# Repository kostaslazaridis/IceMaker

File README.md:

I came across a broken ice maker. Eager to repair it, I discovered that the original PCB was destroyed due to a burned-out IC, making it irreparable. Instead of giving up, I decided to reverse engineer the ice maker's electronics to recreate a working control board from scratch.
https://www.youtube.com/watch?v=2SMoJ112lBk&t=18s

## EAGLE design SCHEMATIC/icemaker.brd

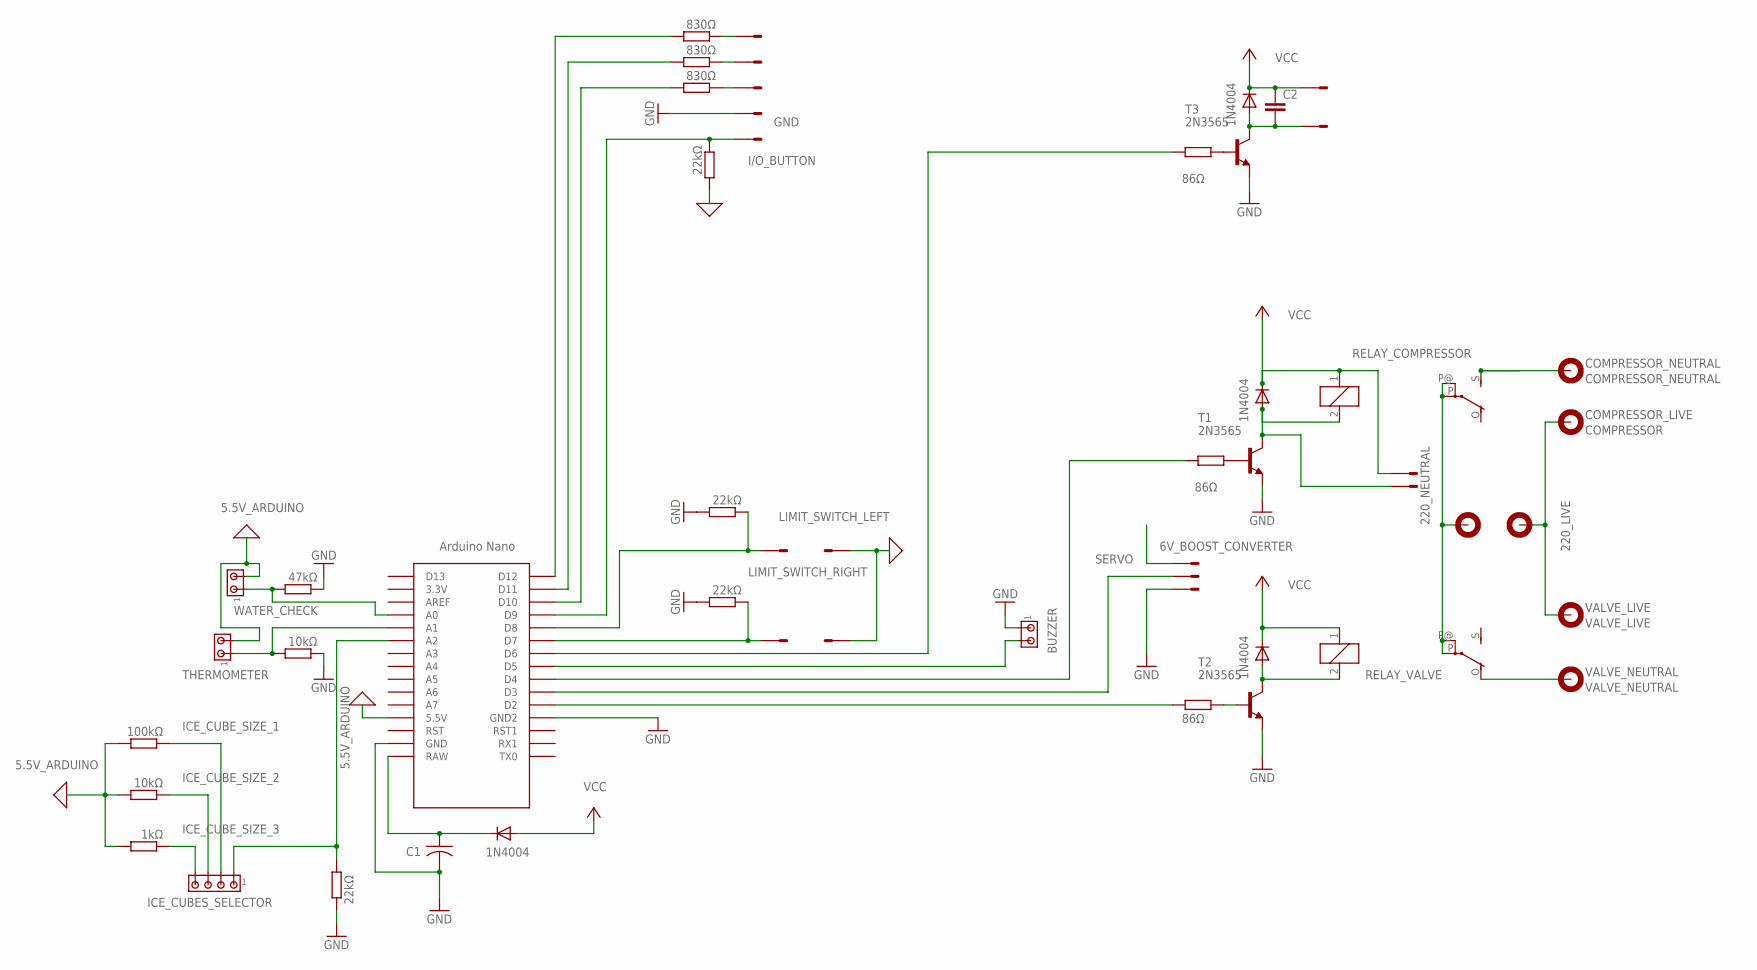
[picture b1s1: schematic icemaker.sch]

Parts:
220_LIVE: 220_LIVE; 2,8-PAD
220_NEUTRLA: 220_NEUTRAL; 2,8-PAD
BUZZER: MTA02-156; 1X2MTA
C1: C-US050-025X075; C050-025X075
C2: C2,5-3; C2.5-3
COMPRESSOR_LIVE: COMPRESSOR; 2,8-PAD
COMPRESSOR_NEUTRAL: COMPRESSOR_NEUTRAL; 2,8-PAD
D1, D2, D3, D4: 1N4004; DO41-10
FAN: L02P
ICE_CUBES_SELECTOR: MTA04-156; 1X4MTA
LED_WORK: I/O_BUTTON; L05P
PUMP: L02P
R1, R2, R3: 86Ω; 0204/5
R4: 1kΩ; 0204/5
R5: 47kΩ; 0204/5
R6, R13: 10kΩ; 0204/5
R7, R8, R9: 830Ω; 0204/5
R10, R11, R12, R16: 22kΩ; 0204/5
R14: 100kΩ; 0204/5
RELAY_COMPRESSOR: M3XXH
RELAY_VALVE: M3XXH
SERVO: S03P
SV1: L04P
T1, T2, T3: 2N3565; TO92
THERMOMETER: MTA02-156; 1X2MTA
U$1: NANO
VALVE_LIVE: VALVE_LIVE; 2,8-PAD
VALVE_NEUTRAL: VALVE_NEUTRAL; 2,8-PAD
WATER_CHECK: MTA02-156; 1X2MTA

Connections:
5.5V_ARDUINO: R4.2, R10.2, R13.2, R14.2, SV1.2, SV1.3, THERMOMETER.2, U$1.5V (5.5V), WATER_CHECK.2
6V_BOOST_CONVERTER: SERVO.3
220V: 220_LIVE.B2,8, COMPRESSOR_LIVE.B2,8, VALVE_LIVE.B2,8
220_NEUTRAL: 220_NEUTRLA.B2,8, RELAY_COMPRESSOR.P, RELAY_COMPRESSOR.P@, RELAY_VALVE.P, RELAY_VALVE.P@
BUZZER: BUZZER.2, U$1.D5
GND: BUZZER.1, C1.2, LED_WORK.2, R5.1, R6.1, R11.2, R12.2, R16.1, SERVO.1, T1.3 (E), T2.3 (E), T3.3 (E), U$1.GND, U$1.GND1 (GND2)
I/O_BUTTON: LED_WORK.1, R10.1, U$1.D9
ICE_CUBE_SIZE_1: ICE_CUBES_SELECTOR.2, R14.1
ICE_CUBE_SIZE_2: ICE_CUBES_SELECTOR.3, R13.1
ICE_CUBE_SIZE_3: ICE_CUBES_SELECTOR.4, R4.1
LIMIT_SWITCH_LEFT: R11.1, SV1.4, U$1.D8
LIMIT_SWITCH_RIGHT: R12.1, SV1.1, U$1.D7
unnamed: D1.A, RELAY_VALVE.2, T2.1 (C)
unnamed: R3.2, U$1.D2
unnamed: R2.2, U$1.D6
unnamed: R2.1, T3.2 (B)
unnamed: R3.1, T2.2 (B)
unnamed: R1.2, U$1.D4
unnamed: LED_WORK.5, R7.1
unnamed: LED_WORK.4, R8.1
unnamed: R7.2, U$1.D12
unnamed: R8.2, U$1.D11
unnamed: R9.2, U$1.D10
unnamed: LED_WORK.3, R9.1
unnamed: R1.1, T1.2 (B)
unnamed: D2.A, FAN.1, RELAY_COMPRESSOR.2, T1.1 (C)
unnamed: C1.1, D3.C, U$1.RAW
unnamed: RELAY_VALVE.O, VALVE_NEUTRAL.B2,8
unnamed: COMPRESSOR_NEUTRAL.B2,8, RELAY_COMPRESSOR.S
unnamed: ICE_CUBES_SELECTOR.1, R16.2, U$1.A2
unnamed: C2.2, D4.A, PUMP.1, T3.1 (C)
SERVO: SERVO.2, U$1.D3
THERMOMETER: R6.2, THERMOMETER.1, U$1.A1
VCC: C2.1, D1.C, D2.C, D3.A, D4.C, FAN.2, PUMP.2, RELAY_COMPRESSOR.1, RELAY_VALVE.1
WATER_CHECK: R5.2, U$1.A0, WATER_CHECK.1

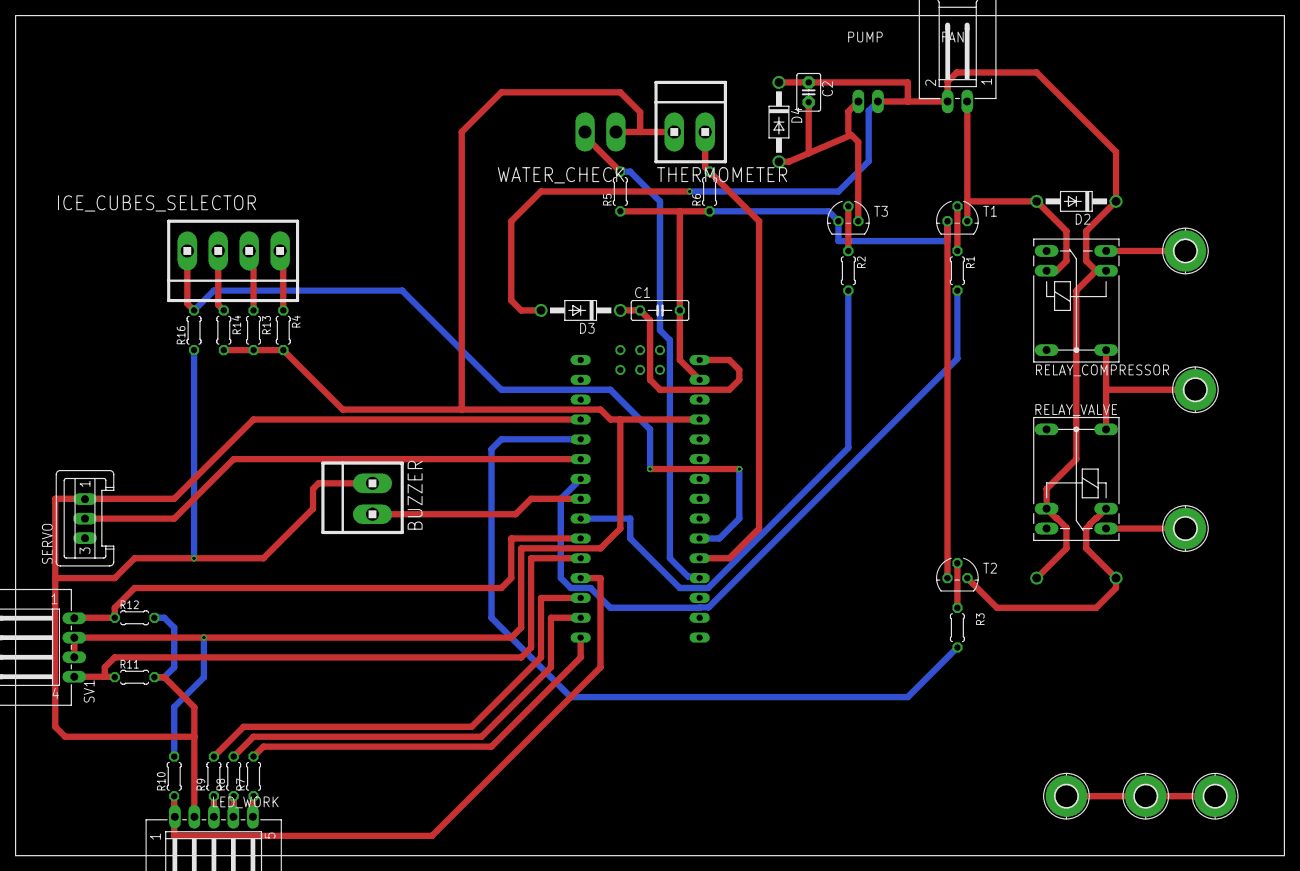
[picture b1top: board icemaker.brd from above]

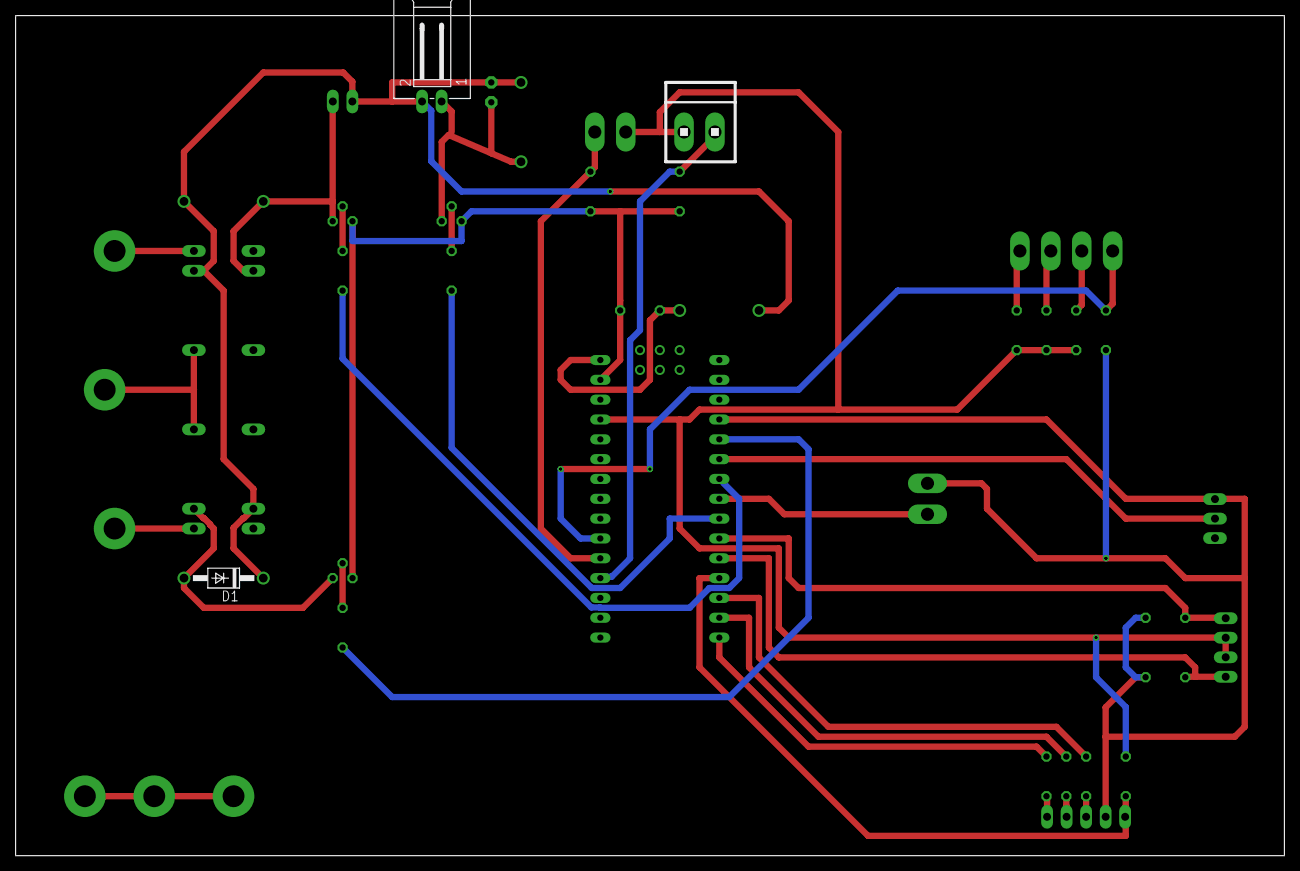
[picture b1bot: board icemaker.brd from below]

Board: 2 copper layers, 162.5 x 107.6 mm, 42 parts (3 on the bottom side), 34 nets.

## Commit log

2020-02-16 class
2020-02-17 working
2020-02-17 end Of project
2020-02-19 final
2020-02-23 end of programm
2022-02-17 IceMaker
